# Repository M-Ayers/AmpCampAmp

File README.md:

# AmpCampAmp

Nelson Pass' Amp Camp Amp V1.6 single channel class A

https://www.firstwatt.com/pdf/art_amp_camp_1.pdf

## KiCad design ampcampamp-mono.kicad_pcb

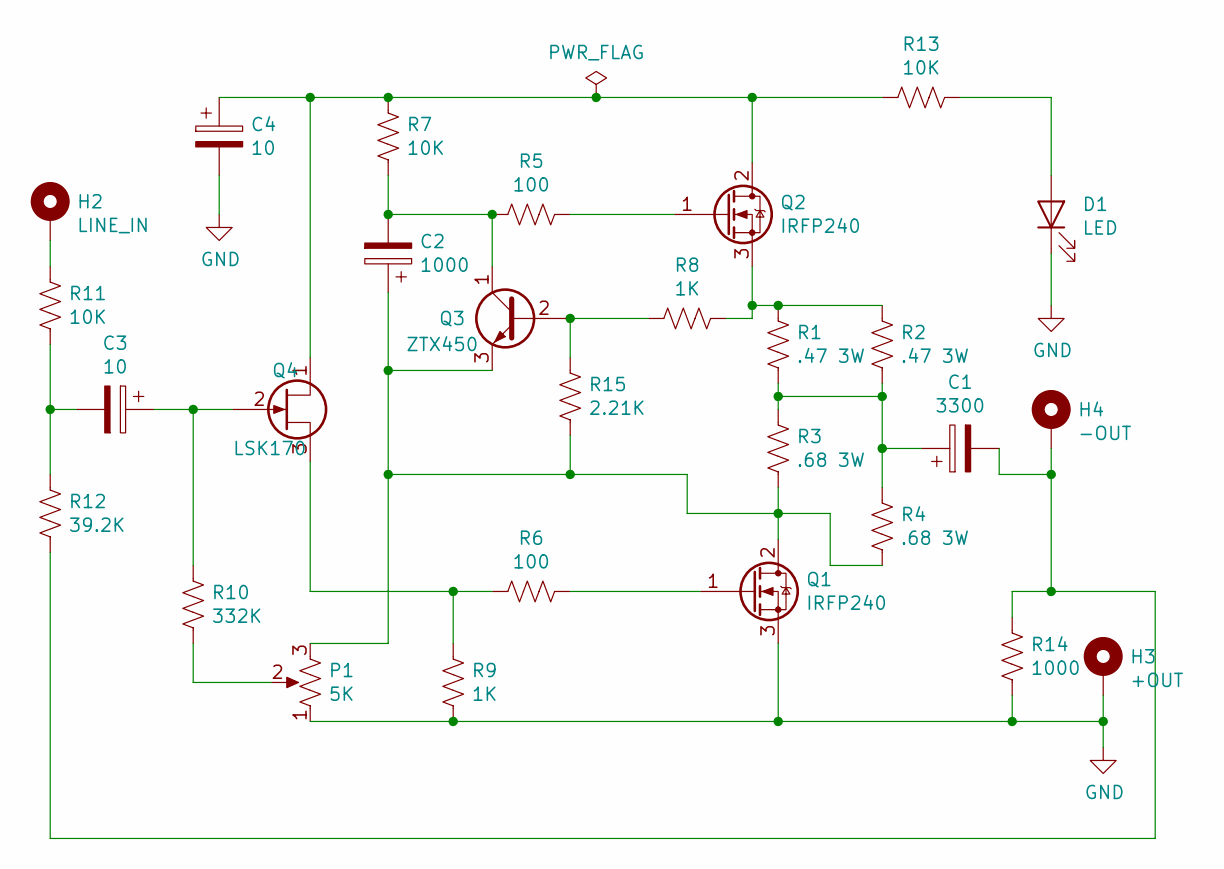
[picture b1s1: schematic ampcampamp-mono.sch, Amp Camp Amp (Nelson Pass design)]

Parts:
C1: 3300; CP_Radial_D22.0mm_P10.00mm_SnapIn
C2: 1000; CP_Radial_D10.0mm_P5.00mm
C3, C4: 10; CP_Radial_D5.0mm_P2.00mm
D1: LED; SolderWirePad_1x02_P3.81mm_Drill1.2mm
H2: LINE_IN; SolderWirePad_1x01_Drill1.2mm
H3: +OUT; SolderWirePad_1x01_Drill1.2mm
H4: -OUT; SolderWirePad_1x01_Drill1.2mm
P1: 5K; Potentiometer_Bourns_3386P_Vertical
Q1, Q2: IRFP240; TO-247-3_Vertical
Q3: ZTX450; TO-92_Inline_Wide
Q4: LSK170; TO-92_Inline_Wide
R1, R2: .47 3W; R_Axial_DIN0614_L14.3mm_D5.7mm_P20.32mm_Horizontal
R3, R4: .68 3W; R_Axial_DIN0614_L14.3mm_D5.7mm_P20.32mm_Horizontal
R5, R6: 100; R_Axial_DIN0207_L6.3mm_D2.5mm_P10.16mm_Horizontal
R7, R11, R13: 10K; R_Axial_DIN0207_L6.3mm_D2.5mm_P10.16mm_Horizontal
R8, R9: 1K; R_Axial_DIN0207_L6.3mm_D2.5mm_P10.16mm_Horizontal
R10: 332K; R_Axial_DIN0207_L6.3mm_D2.5mm_P10.16mm_Horizontal
R12: 39.2K; R_Axial_DIN0207_L6.3mm_D2.5mm_P10.16mm_Horizontal
R14: 1000; R_Axial_DIN0207_L6.3mm_D2.5mm_P10.16mm_Horizontal
R15: 2.21K; R_Axial_DIN0207_L6.3mm_D2.5mm_P10.16mm_Horizontal

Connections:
GND: C4.2, D1.1 (K), H3.1, P1.1, Q1.3 (S), R9.2, R14.2
unnamed: C1.1, R1.2, R2.2, R3.1, R4.1
unnamed: C1.2, H4.1, R12.2, R14.1
unnamed: C2.1, P1.3, Q1.2 (D), Q3.3 (E), R3.2, R4.2, R15.2
unnamed: C2.2, Q3.1 (C), R5.2, R7.1
unnamed: C3.1, Q4.2 (G), R10.1
unnamed: C3.2, R11.2, R12.1
unnamed: C4.1, Q2.2 (D), Q4.1 (D), R7.2, R13.2
unnamed: D1.2 (A), R13.1
unnamed: H2.1, R11.1
unnamed: P1.2, R10.2
unnamed: Q1.1 (G), R6.1
unnamed: Q2.1 (G), R5.1
unnamed: Q2.3 (S), R1.1, R2.1, R8.1
unnamed: Q3.2 (B), R8.2, R15.1
unnamed: Q4.3 (S), R6.2, R9.1

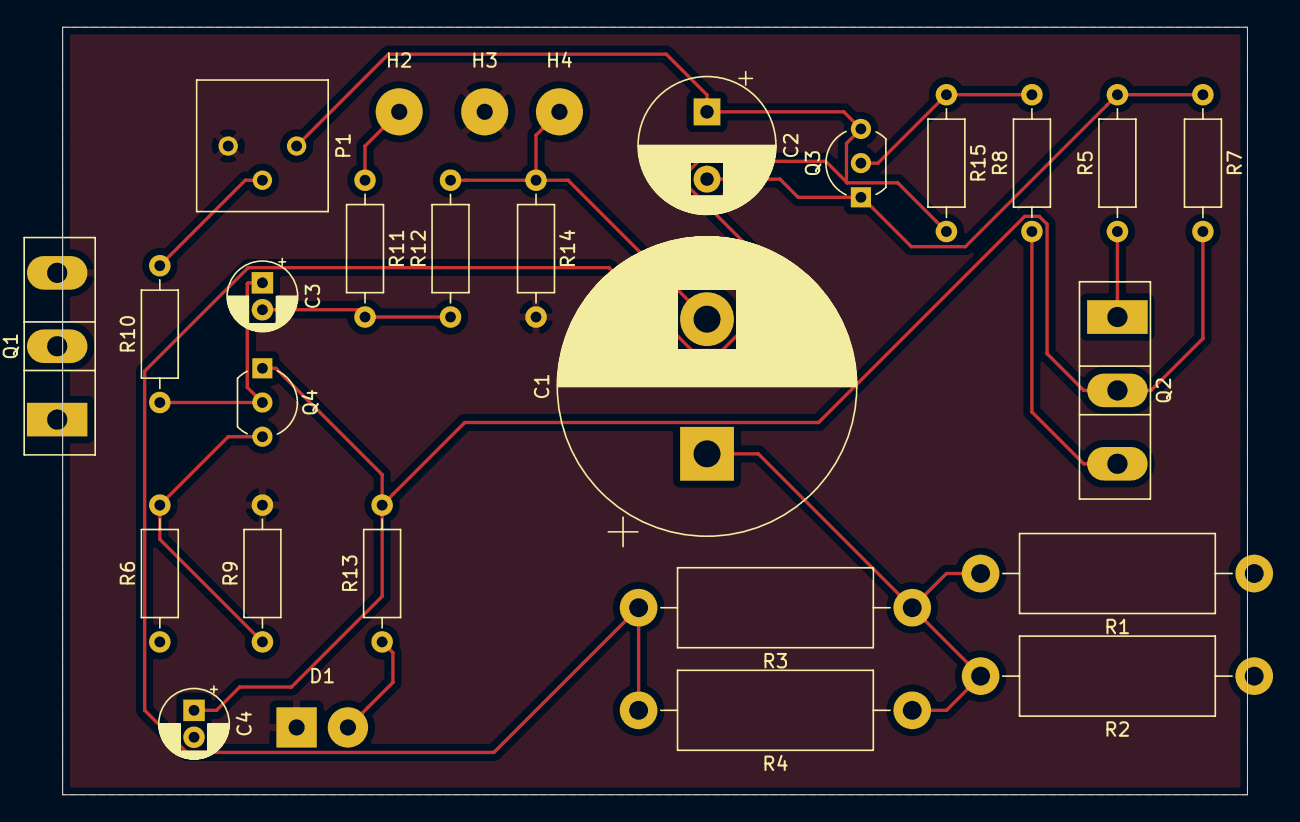
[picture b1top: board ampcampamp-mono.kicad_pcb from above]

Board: 2 copper layers, 88.0 x 57.0 mm, 28 parts (0 on the bottom side), 16 nets.

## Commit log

2021-05-10 init
